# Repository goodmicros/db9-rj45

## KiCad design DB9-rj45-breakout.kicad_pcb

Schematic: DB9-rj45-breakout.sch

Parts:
CN1: 1x9; DB9-slim
CN2: 1x8; RJHSE-5080
SW1: spdt; 100SP1T1B4M2QE

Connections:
/5V: CN1.7, CN2.8
/GND: CN1.8, CN2.1
/a: CN1.6, CN2.6
/b: CN1.9, SW1.3
/down: CN1.2, CN2.3
/left: CN1.3, CN2.4
/right: CN1.4, CN2.5
/up: CN1.1, CN2.2, SW1.1
unnamed: CN2.7, SW1.2

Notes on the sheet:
amiga
RJ45

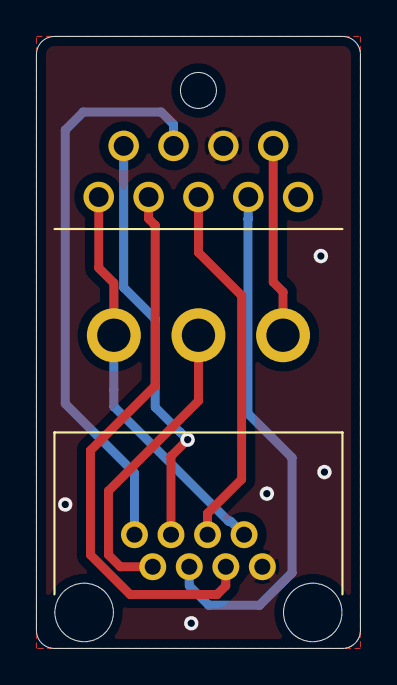
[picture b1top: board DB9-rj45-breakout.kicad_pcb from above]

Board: 2 copper layers, 18.0 x 34.0 mm, 3 parts (0 on the bottom side), 9 nets.

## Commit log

2020-11-26 first version
2020-11-26 fixed crooked 5V track
2020-11-26 fixed flipped rj-45 connector on schema
2020-11-26 removed backup file, added step model
2020-12-11 b toggle conf
2020-12-13 added toggle switch to select up button
2020-12-13 updated bottom silk
2020-12-27 cleaned up silkscreen from overlapping pcb edges
2021-04-14 fixed switch to choose 2nd button between up and 2nd button
2021-04-14 slimmed board down so the DB9 connector can be cut to size
2021-08-06 changed DB9 pinout to female
